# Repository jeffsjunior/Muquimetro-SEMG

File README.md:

# Muquimetro-SEMG 

## Eletromiografia de Superfície

## Sobre o Projeto

  O Muquímetro é um dispositivo eletrônico que mede a ativação muscular a partir do potencial de ação gerado pelos neurônios motores. A medição ocorre na superfície da pele, por isso o nome Eletromiografia de Superfície (SEMG). A eletromiografia de superfície vem sendo bastante utilizada em diversas áreas, por exemplo, medicina, fisioterapia, robótica, terapia ocupacional. O Muquímetro foi desenvolvido por alunos e professores da Universidade Federal de Sergipe durante a disciplina Eletrônica Aplicada, ofertada pelo curso Engenharia Eletrônica do Departamento de Engenharia Elétrica.

### Aplicações
* Robótica
* Jogos
* Estudo da atividade muscular
* Testes de força, exaustão e fadiga muscular
* Fisioterapia esportiva

## Licença
Todo o material e o Muquímetro estão licenciados de acordo com TAPR Open Hardware License (OHL). O documento contendo informações a respeito da licença encontra-se no arquivo “LICENSE.pdf”.

## Contato

Jefferson Silveira - descomplexando@gmail.com

Link do Projeto: [https://github.com/jeffsjunior/Muquimetro-SEMG](https://github.com/jeffsjunior/Muquimetro-SEMG)

## Participantes do Projeto
* André de Andrade
* Carlos Silva
* Hugo Fontes
* Lean de Oliveira
* Lucas Castro
* Micaelle de Souza
* Raphael Cardoso
* Raul de Andrade
* Renan Sandes
* Renato Fagundes
* Ruan dos Santos
* Shyenne Souza

# Desenvolvido na

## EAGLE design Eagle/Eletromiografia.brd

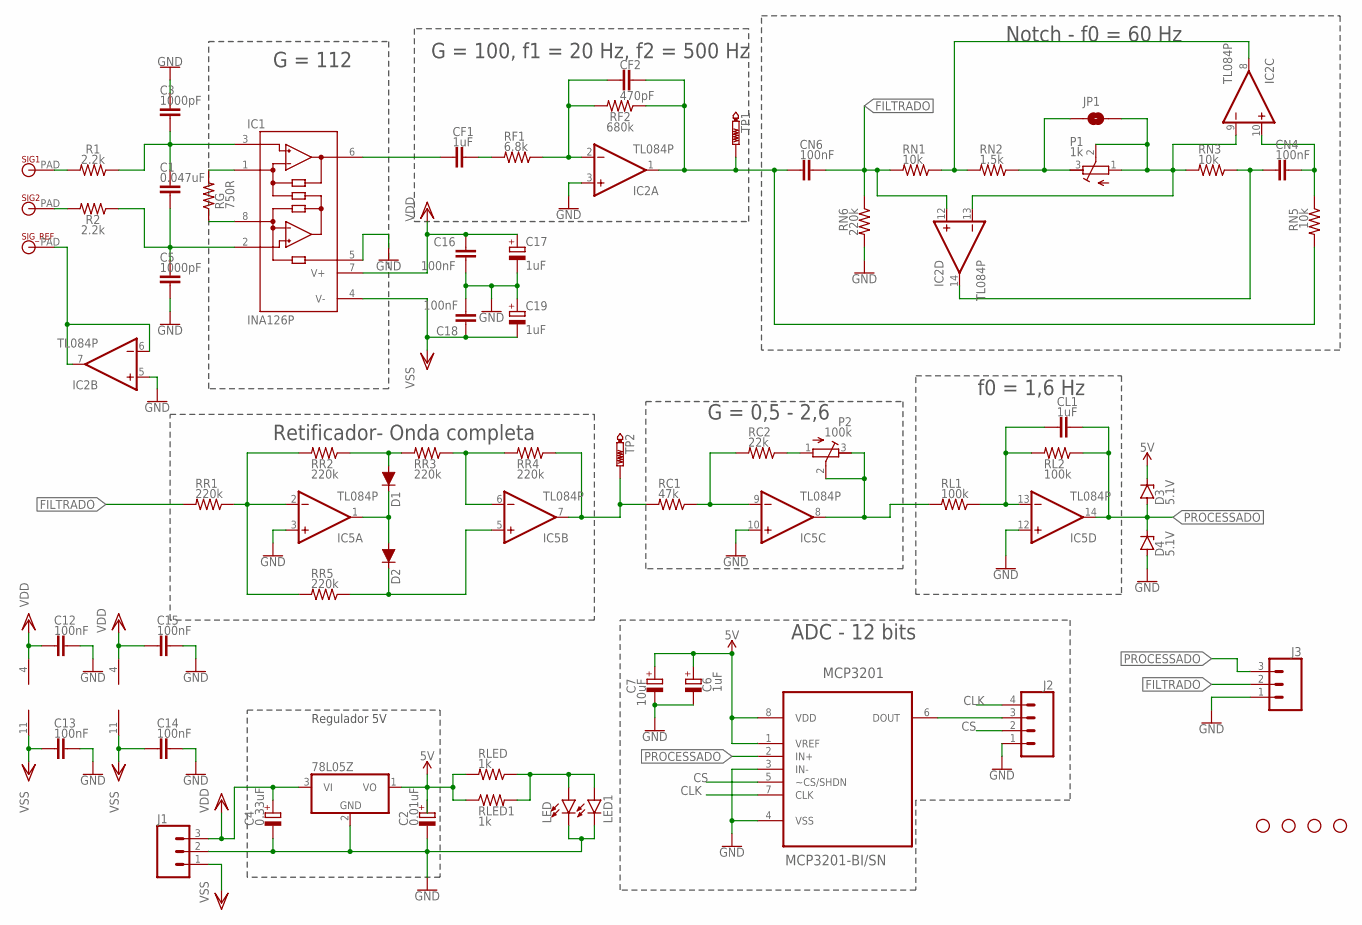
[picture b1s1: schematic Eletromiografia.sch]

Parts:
C1: 0.047uF; C025-025X050
C2: 0.01uF; E2,5-6
C3, C5: 1000pF; C025-025X050
C4: 0.33uF; E2,5-6
C6, C17, C19: 1uF; E2,5-6
C7: 10uF; E2,5-6
C12, C13, C14, C15, C16, C18: 100nF; C025-025X050
CF1: 1uF; C025-025X050
CF2: 470pF; C025-025X050
CL1: 1uF; C025-025X050
CN4, CN6: 100nF; C025-025X050
D1, D2: 200mA/100V/1V; DIODE-1N4148
D3, D4: 5.1V; ZDIO-7.5
H1, H2, H3, H4: STAND-OFFTIGHT; STAND-OFF-TIGHT
IC1: INA126P; DIL08
IC2, IC5: TL084P; DIL14
IC3: 78L05Z; TO92
J1: CONN_03LONGPADS; 1X03_LONGPADS
J2: CONN_041X04_NO_SILK; 1X04_NO_SILK
J3: CONN_031X03_NO_SILK; 1X03_NO_SILK
JP1: JUMPER-SMT_2_NO_NO-SILK_ROUND; SMT-JUMPER_2_NO_NO-SILK_ROUND
LED: LED3MM; LED_3MM
LED1: LEDCHIP-LED0805; CHIP-LED0805
MCP3201: MCP3201-BI/SN; SOIC127P600X175-8N
P1: 1k; RTRIM64W
P2: 100k; RTRIM64W
R1, R2: 2.2k; 0207/10
RC1: 47k; 0207/10
RC2: 22k; 0207/10
RF1: 6.8k; 0207/10
RF2: 680k; 0207/10
RG: 750R; 0207/10
RL1, RL2: 100k; 0207/10
RLED: 1k; 0207/10
RLED1: 1k; R0805
RN1, RN3, RN5: 10k; 0207/10
RN2: 1.5k; 0207/10
RN6: 220k; 0207/10
RR1, RR2, RR3, RR4, RR5: 220k; 0207/10
SIG1, SIG2: MICROBIT_PAD
SIG_REF: MICROBIT_PAD
TP1, TP2: PTR1B1,27; B1,27

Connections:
5V: C2.+, C6.+, C7.+, D3.C, IC3.1 (VO), MCP3201.1 (VREF), MCP3201.8 (VDD), RLED.2, RLED1.1
CLK: J2.4, MCP3201.7 (CLK)
CS: J2.2, MCP3201.5 (~CS/SHDN)
FILTRADO: CN6.2, IC2.12 (+IN), J3.2, RN1.2, RN6.1, RR1.2
GND: C2.-, C3.2, C4.-, C5.1, C6.-, C7.-, C12.2, C13.2, C14.2, C15.2, C16.1, C17.-, C18.2, C19.+, D4.A, IC1.5 (REF), IC2.3 (+IN), IC2.5 (+IN), IC3.2 (GND), IC5.3 (+IN), IC5.10 (+IN), IC5.12 (+IN), J1.2, J2.1, J3.1, LED.K (C), LED1.C, MCP3201.3 (IN-), MCP3201.4 (VSS), RN6.2
unnamed: IC1.1 (RG), RG.2
unnamed: IC1.8 (RG), RG.1
unnamed: C1.2, C3.1, IC1.3 (+IN), R1.1
unnamed: R1.2, SIG1.PAD
unnamed: IC2.6 (-IN), IC2.7 (OUT), SIG_REF.PAD
unnamed: CF1.1, IC1.6 (OUT)
unnamed: CF1.2, RF1.2
unnamed: CF2.1, IC2.2 (-IN), RF1.1, RF2.2
unnamed: JP1.1, P1.3 (E), RN2.1
unnamed: CF2.2, CN6.1, IC2.1 (OUT), RF2.1, RN5.2, TP1.TP
unnamed: CN4.2, IC2.10 (+IN), RN5.1
unnamed: CN4.1, IC2.14 (OUT), RN3.1
unnamed: C1.1, C5.2, IC1.2 (-IN), R2.1
unnamed: R2.2, SIG2.PAD
unnamed: IC2.8 (OUT), RN1.1, RN2.2
unnamed: IC2.9 (-IN), IC2.13 (-IN), JP1.2, P1.1 (A), P1.2 (S), RN3.2
unnamed: J2.3, MCP3201.6 (DOUT)
unnamed: IC5.2 (-IN), RR1.1, RR2.2, RR5.2
unnamed: D1.A, RR2.1, RR3.2
unnamed: D1.C, D2.A, IC5.1 (OUT)
unnamed: D2.C, IC5.5 (+IN), RR5.1
unnamed: IC5.6 (-IN), RR3.1, RR4.2
unnamed: IC5.7 (OUT), RC1.2, RR4.1, TP2.TP
unnamed: IC5.9 (-IN), RC1.1, RC2.2
unnamed: P2.1 (A), RC2.1
unnamed: IC5.8 (OUT), P2.2 (S), P2.3 (E), RL1.2
unnamed: CL1.1, IC5.13 (-IN), RL1.1, RL2.2
unnamed: LED.A, LED1.A, RLED.1, RLED1.2
PROCESSADO: CL1.2, D3.A, D4.C, IC5.14 (OUT), J3.3, MCP3201.2 (IN+), RL2.1
VDD: C4.+, C12.1, C15.1, C16.2, C17.+, IC1.7 (V+), IC2.4 (V+), IC3.3 (VI), IC5.4 (V+), J1.3
VSS: C13.1, C14.1, C18.1, C19.-, IC1.4 (V-), IC2.11 (V-), IC5.11 (V-), J1.1

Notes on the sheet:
G = 112
G = 100, f1 = 20 Hz, f2 = 500 Hz
Notch - f0 = 60 Hz
Retificador- Onda completa
G = 0,5 - 2,6
f0 = 1,6 Hz
ADC - 12 bits
Regulador 5V

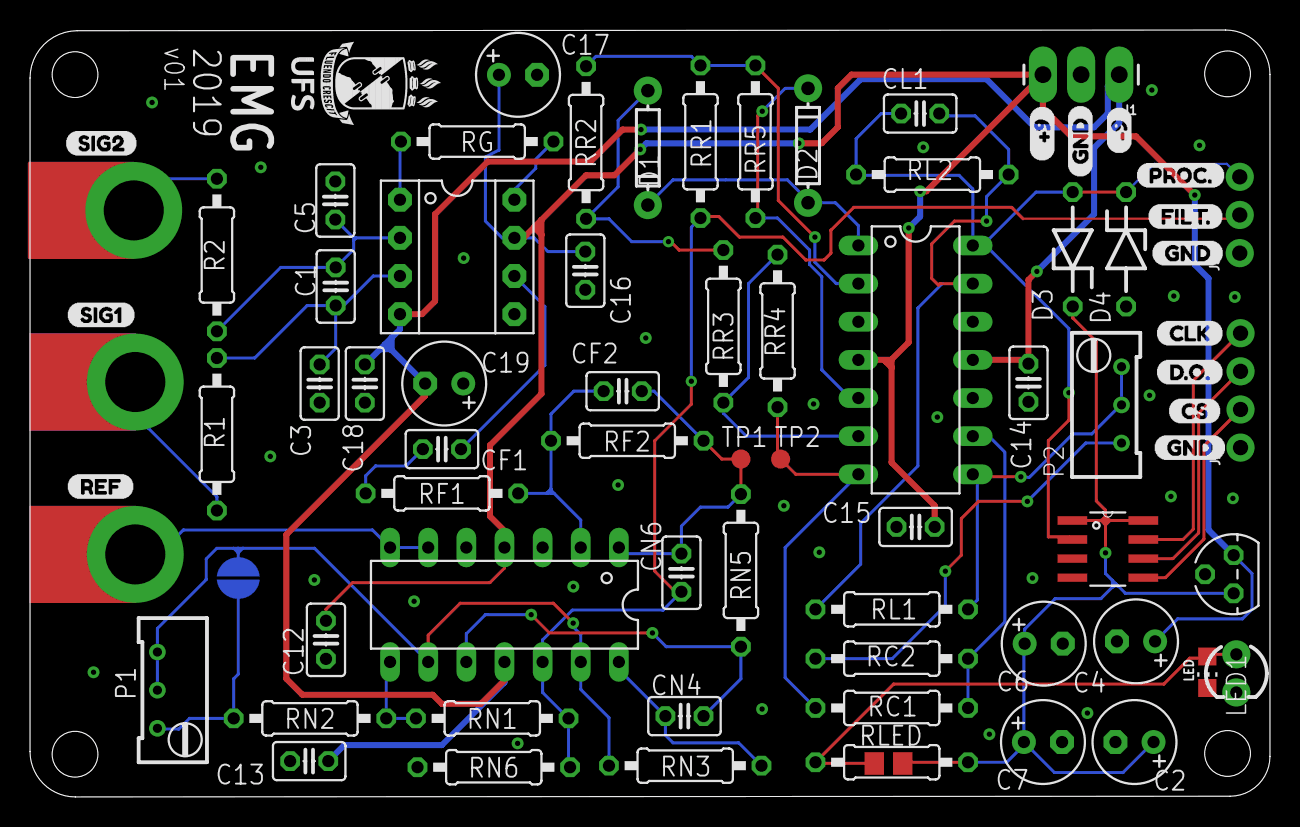
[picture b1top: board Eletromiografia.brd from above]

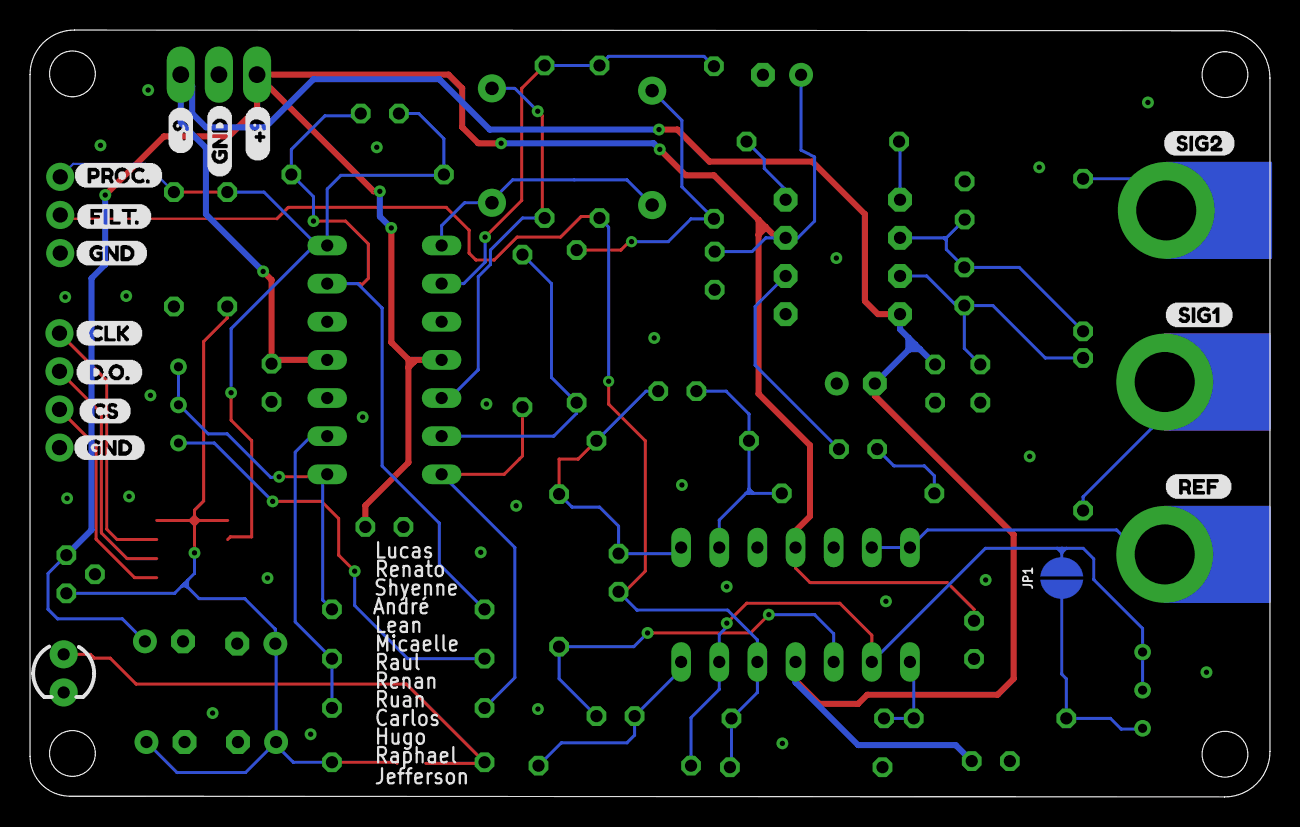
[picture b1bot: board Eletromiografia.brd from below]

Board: 2 copper layers, 82.6 x 51.1 mm, 93 parts (14 on the bottom side), 36 nets.

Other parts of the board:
U$2, U$18: _#98
U$3, U$20: #99
U$4, U$7, U$11, U$19, U$23, U$27: GND7
U$5, U$21: PROC#3
U$6, U$22: FILT#4
U$8, U$24: CLK6
U$9, U$25: D#O#10
U$10, U$26: CS5
U$12, U$15: SIG21
U$13, U$16: SIG12
U$14, U$17: REF0

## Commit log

2019-11-14 Adicionando arquivos originais
2019-11-14 Adicionando folders
2019-11-14 Adicionando imagem extra

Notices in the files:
parts and their libraries:
SparkFun-Connectors: Licensing: Creative Commons ShareAlike 4.0 International - https://creativecommons.org/licenses/by-sa/4.0
